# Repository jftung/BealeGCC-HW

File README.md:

# BealeGCC-HW
Seperate repository for the hardware used in the BealeGCC

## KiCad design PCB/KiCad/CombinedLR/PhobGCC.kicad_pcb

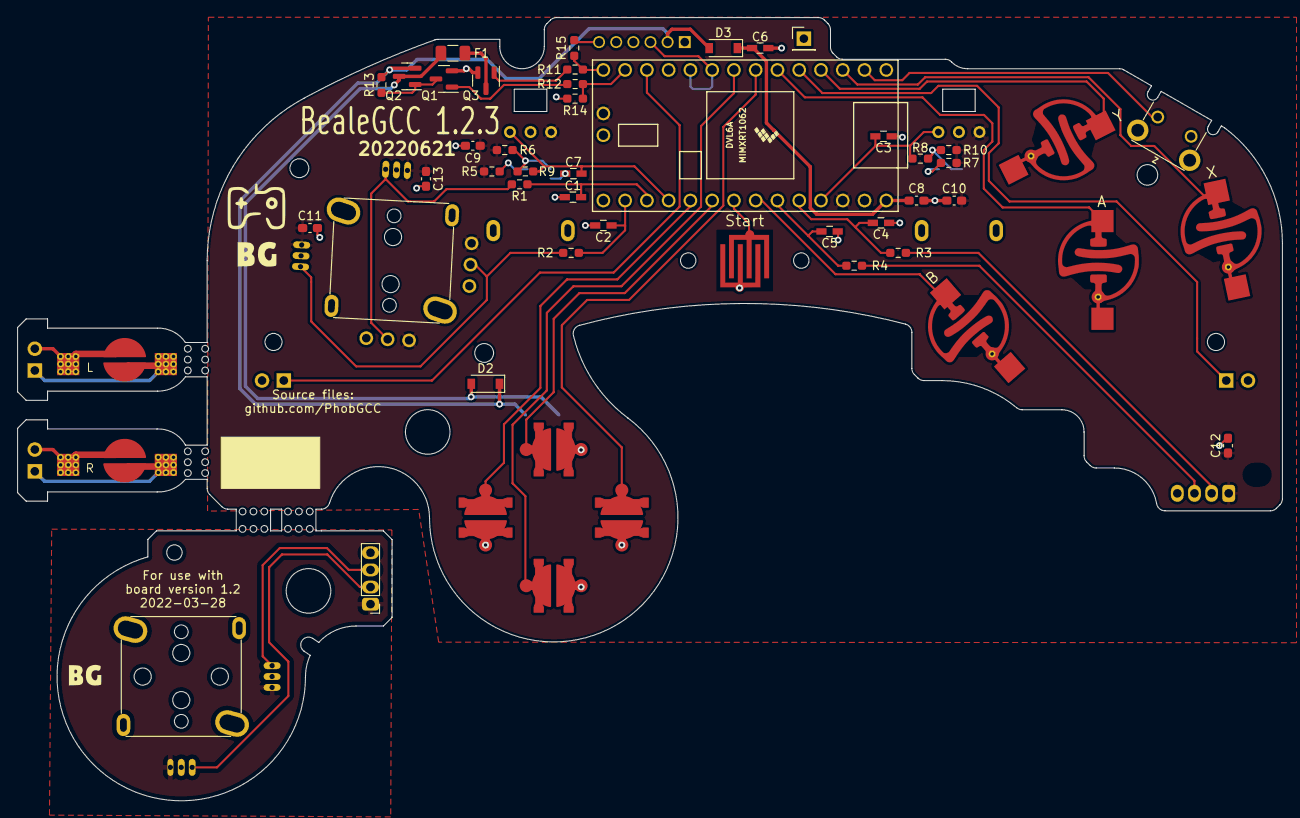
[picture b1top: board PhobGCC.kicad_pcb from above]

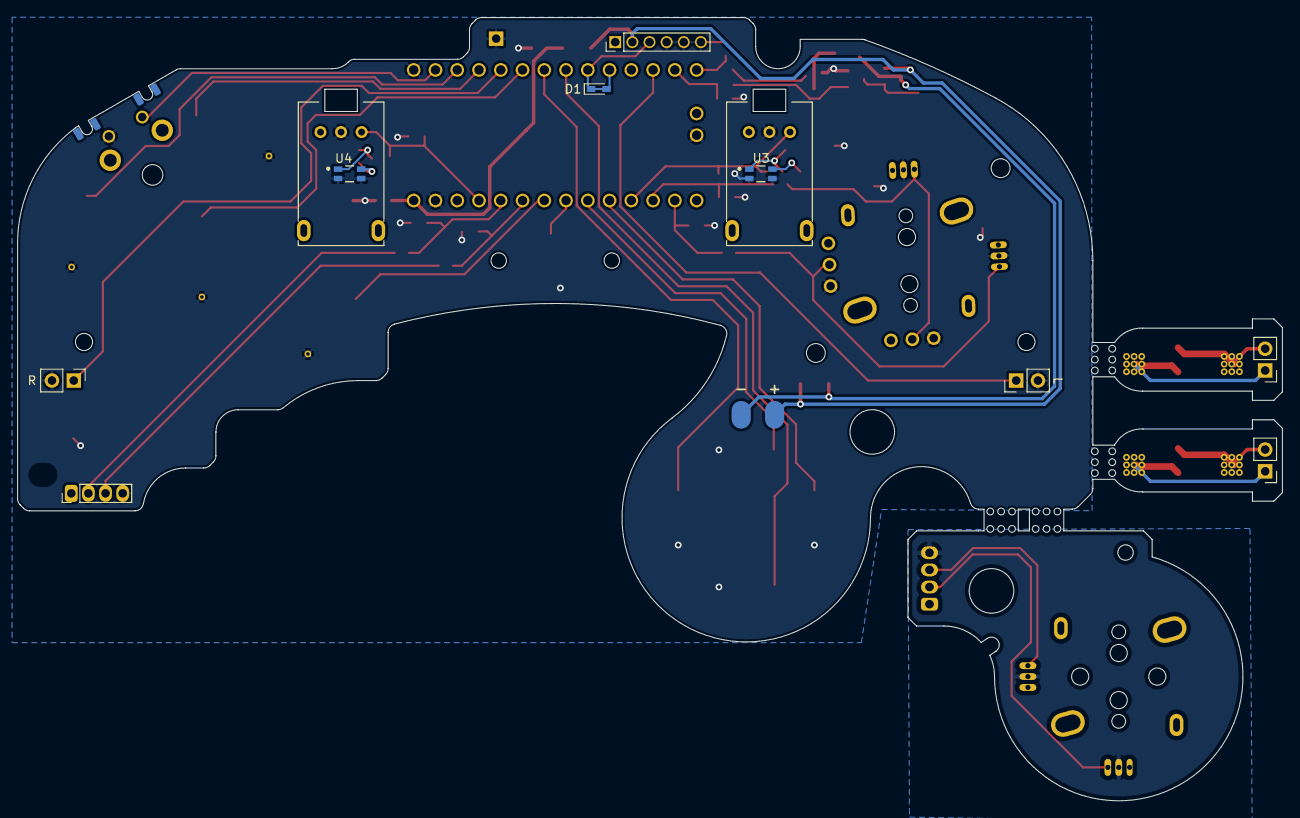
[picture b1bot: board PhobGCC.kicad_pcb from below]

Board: 2 copper layers, 147.6 x 91.4 mm, 80 parts (12 on the bottom side), 45 nets.

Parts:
C1, C2, C3, C4, C5, C7: 0.047u; C_0603_HandSoldering
C6: 10u; C_0603_HandSoldering
C8, C9, C10, C11, C12, C13: 1u; C_0603_1608Metric_Pad1.08x0.95mm_HandSolder
D1: D_Schottky_Shorted; D_SOD-523_Shorted
D2, D3: M7C; D_SOD-123
F1: Fuse; Fuse_1206_3216Metric
H1: 5.2mm; MountingHole_5.2mm
H2: Slot
H3, H4: 2mm; MountingHole_2.0mm
H5, H6: 1.8mm; MountingHole_1.8mm
H7: 2.4mm; MountingHole_2.4mm
H8, H9: 2.2mm; MountingHole_2.2mm
H10: MountingHole; MountingHole_1.8mm
H11: MountingHole; MountingHole_5.2mm
H12, H13: MountingHole; MountingHole_2.0mm
H14, H15: MouseBite; breakaway-mousebites-double
H16: MouseBiteLA; breakaway-mousebites-double
H17: MouseBiteRA; breakaway-mousebites-double
J1: Conn_01x06_Female; GCC_Header_Straight_1x06_Pitch2.00mm
J2: Conn_01x04_Female; PinHeader_1x04_P2.00mm_Vertical
J3: Conn_01x01_Male; PinHeader_1x01_P2.54mm_Vertical
J4: Conn_01x04_Male; PinHeader_1x04_P2.00mm_Vertical
J5: Rumble; rumble_pins
J6: L; Pin_Header_Straight_1x02_Pitch2.54mm
J7: R; Pin_Header_Straight_1x02_Pitch2.54mm
Q1, Q3: Q_NMOS_GSD; SOT-23
Q2: Q_PMOS_GDS; SOT-23
R1, R2, R3, R4: 2k; R_0603_1608Metric_Pad0.98x0.95mm_HandSolder
R5, R6, R7, R8, R9, R10: DNP; R_0603_1608_DNP
R11, R12: 100R; R_0603_1608Metric_Pad0.98x0.95mm_HandSolder
R13, R14, R15: 10k; R_0603_1608Metric_Pad0.98x0.95mm_HandSolder
RV1, RV2: R_POT_MountingPin; GCC_Slider
SW1: A; ABXY_Contact_Omron_Switch
SW2: B; ABXY_Contact_Omron_Switch
SW3: X; ABXY_Contact_Omron_Switch
SW4: Y; ABXY_Contact_Omron_Switch
SW5: Start; Start_Contact
SW6: L; Pin_Header_Straight_1x02_Pitch2.54mm
SW7: R; Pin_Header_Straight_1x02_Pitch2.54mm
SW8: Z; Z_Switch_Edge_Omron
SW9: Dleft; Dpad_Contact_TL3315NF_2
SW10: Dup; Dpad_Contact_TL3315NF_2
SW11: Dright; Dpad_Contact_TL3315NF_2
SW12: Ddown; Dpad_Contact_TL3315NF_2
SW13: L; Trigger_Contact
SW14: R; Trigger_Contact
U1: Teensy4.0; Teensy40_Edge_Pins
U2: 2x DRV5053CAQLPGM Hall Effect Sensors; GCC_Stickbox_2
U3, U4: GP2S60-MFG; Sharp_Microelectronics-GP2S60-MFG
U5: Stickbox_Assembly; GCC_Stickbox_Hall_Only

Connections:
+3V3: C9.1, C10.1, C11.1, C12.1, C13.1, J2.1, R5.1, R6.1, R7.1, R10.1, RV1.1 (V+), RV2.1 (V+), U1.16 (3V3), U1.31 (3V3), U2.1 (H1XV), U2.4 (H1YV), U2.15 (P1XV), U2.18 (P1YV)
+5V: D2.1 (K), D3.2 (A), J1.2, J5.1, Q2.2 (S), R13.2
/A: SW1.1, U1.6 (4_BCLK2)
/B: SW2.1, U1.27 (20_A6_TX5_LRCLK1)
/Brake: R12.1, R14.2, U1.13 (11_MOSI_CTX1)
/C_x: J2.2, R3.2
/C_x_filt: C4.1, R3.1, U1.29 (22_A8_CTX1)
/C_y: J2.3, R4.2
/C_y_filt: C5.1, R4.1, U1.28 (21_A7_RX5_BCLK1)
/Data: D1.1 (K), D1.2 (A), J1.3, U1.9 (7_RX2_OUT1A), U1.10 (8_TX2_IN1)
/Ddown: SW12.1, U1.8 (6_OUT1D)
/Dleft: SW9.1, U1.24 (17_A3_TX4_SDA1)
/Dright: SW11.1, U1.7 (5_IN2)
/Dup: SW10.1, U1.25 (18_A4_SDA0)
/L: SW6.1, U1.12 (10_CS_MQSR)
/Lanalog: C7.1, R9.2, RV1.3 (Signal), U1.23 (16_A2_RX4_SCL1)
/R: SW7.1, U1.5 (3_LRCLK2)
/Ranalog: C3.1, R8.2, RV2.3 (Signal), U1.30 (23_A9_CRX1_MCLK1)
/Rumble: R11.1, R15.2, U1.14 (12_MISO_MQSL)
/Start: SW5.1, U1.26 (19_A5_SCL0)
/Stick_x: R1.2, U2.3 (H1XS), U2.14 (P1XS)
/Stick_x_filt: C1.1, R1.1, U1.22 (15_A1_RX3_SPDIF_IN)
/Stick_y: R2.2, U2.6 (H1YS), U2.17 (P1YS)
/Stick_y_filt: C2.1, R2.1, U1.21 (14_A0_TX3_SPDIF_OUT)
/X: SW3.1, U1.3 (1_TX1_CTX2_MISO1)
/Y: SW4.1, U1.4 (2_OUT2)
/Z: SW8.1, U1.2 (0_RX1_CRX2_CS1)
GND: C1.2, C2.2, C3.2, C4.2, C5.2, C6.2, C7.2, C8.2, C9.2, C10.2, C11.2, C12.2, C13.2, J1.4, J1.5, J1.6, J2.4, J3.1, J4.4, Q1.2 (S), Q3.2 (S), R14.1, R15.1, RV1.2 (GND), RV2.2 (GND), SW1.2, SW2.2, SW3.2, SW4.2, SW5.2, SW6.2, SW7.2, SW8.2, SW9.2, SW10.2, SW11.2, SW12.2, U1.1 (GND), U1.17 (GND), U1.32 (GND), U2.2 (H1XG), U2.5 (H1YG), U2.13 (P1XG), U2.16 (P1YG), U3.2 (E), U3.3 (K), U4.2 (E), U4.3 (K), U5.2 (H1XG), U5.5 (H1YG)
unnamed: C6.1, C8.1, D3.1 (K), U1.33 (VIN)
unnamed: D2.2 (A), F1.1, J5.2, Q2.3 (D)
unnamed: F1.2, Q3.3 (D)
unnamed: J4.2, U5.3 (H1XS)
unnamed: J4.3, U5.6 (H1YS)
unnamed: J6.1, SW13.1
unnamed: J6.2, SW13.2
unnamed: J7.1, SW14.1
unnamed: J7.2, SW14.2
unnamed: Q1.1 (G), R12.2
unnamed: Q1.3 (D), Q2.1 (G), R13.1
unnamed: Q3.1 (G), R11.2
unnamed: R5.2, U3.4 (A)
unnamed: R6.2, R9.1, U3.1 (C)
unnamed: R7.2, U4.4 (A)
unnamed: R8.1, R10.2, U4.1 (C)
VCC: J4.1, U5.1 (H1XV), U5.4 (H1YV)

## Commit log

2022-07-25 Replace PhobGCC text/logos with BealeGCC & BG logo
    Add full Beale Gaming (BG) logo and small BG logo png files. Convert
    these into two kicad_mod files: a 10mm footprint for the full logo and a
    4mm footprint for the small logo. On the CombinedLR PCB, replace the
    large ghost with the full logo, the small ghost with the small logo, and
    the "PhobGCC" text with "BealeGCC". The Motherboard, CStick, and
    Combined PCBs are unchanged. Update the README to say "BealeGCC".
